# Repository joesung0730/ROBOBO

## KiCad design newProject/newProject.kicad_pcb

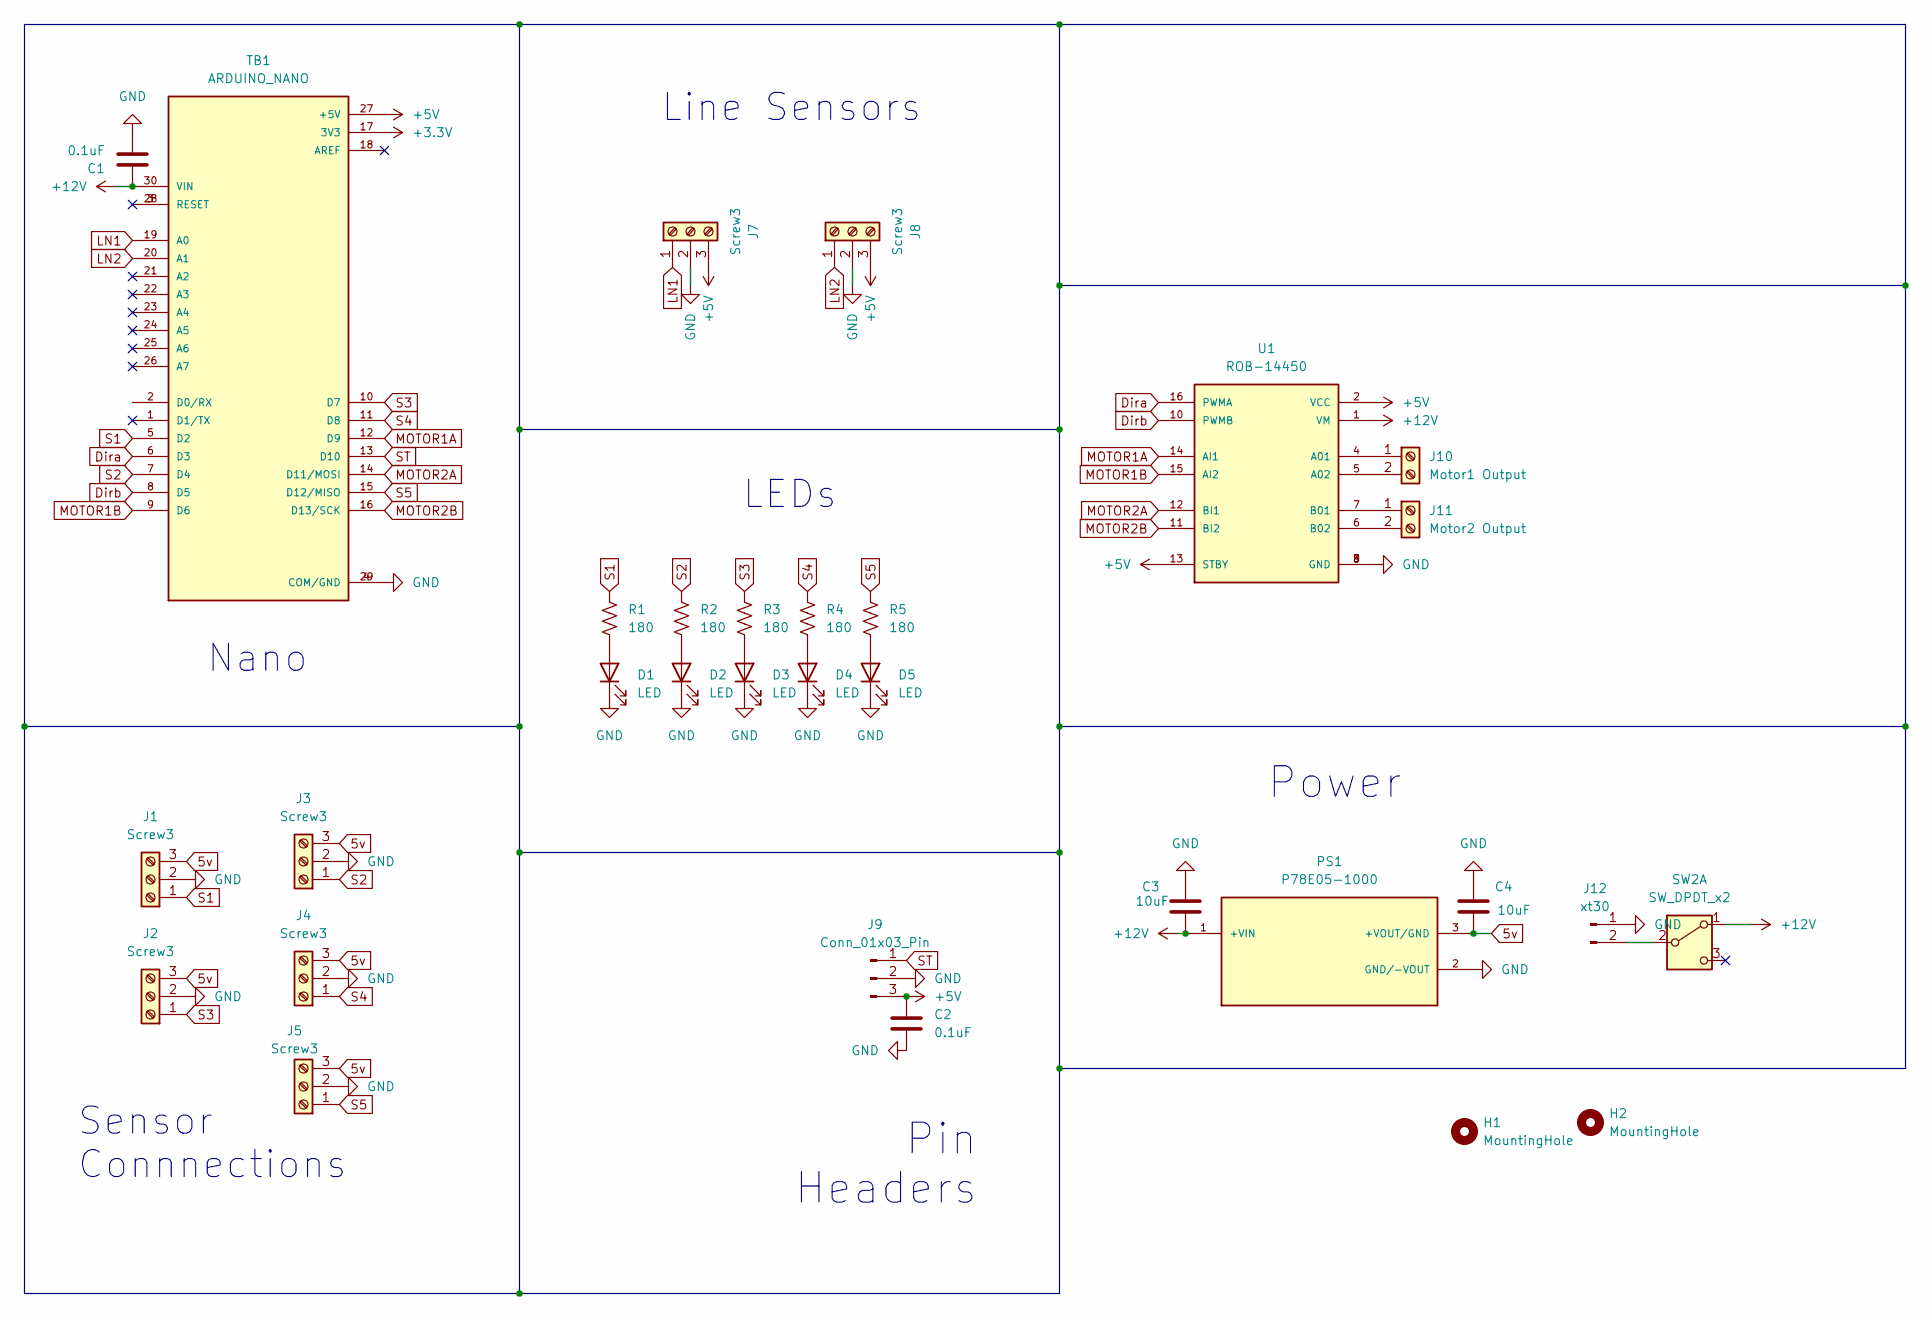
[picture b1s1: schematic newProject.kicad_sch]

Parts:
C1, C2: 0.1uF; C_0805_2012Metric
C3, C4: 10uF; C_0805_2012Metric
D1, D2, D3, D4, D5: LED; LED_1206_3216Metric
H1, H2: MountingHole; MountingHole_2.5mm
J1, J2, J3, J4, J5, J8: Screw3; JST_EH_B3B-EH-A_1x03_P2.50mm_Vertical
J7: Screw3; PinHeader_1x03_P2.54mm_Vertical
J9: Conn_01x03_Pin; PinHeader_1x03_P2.54mm_Vertical
J10: Motor1 Output; PinHeader_1x02_P2.54mm_Vertical
J11: Motor2 Output; PinHeader_1x02_P2.54mm_Vertical
J12: xt30; AMASS_XT30U-F_1x02_P5.0mm_Vertical
PS1: P78E05-1000; CONV_P78E05-1000
R1, R2, R3, R4, R5: 180; R_0805_2012Metric
SW2: SW_DPDT_x2; PinHeader_1x03_P2.54mm_Vertical
TB1: ARDUINO_NANO; Arduino_Nano
U1: ROB-14450; MODULE_ROB-14450; PARTREV 11-13-17

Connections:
5v: C4.1, J1.3, J2.3, J3.3, J4.3, J5.3, PS1.3 (+VOUT/GND)
+3.3V: TB1.17 (3V3)
+5V: C2.1, J7.3, J8.3, J9.3, TB1.27 (+5V), U1.2 (VCC), U1.13 (STBY)
+12V: C1.1, C3.1, PS1.1 (+VIN), SW2.1 (A), TB1.30 (VIN), U1.1 (VM)
Dira: TB1.6 (D3), U1.16 (PWMA)
Dirb: TB1.8 (D5), U1.10 (PWMB)
GND: C1.2, C2.2, C3.2, C4.2, D1.1 (K), D2.1 (K), D3.1 (K), D4.1 (K), D5.1 (K), J1.2, J2.2, J3.2, J4.2, J5.2, J7.2, J8.2, J9.2, J12.1, PS1.2 (GND/-VOUT), TB1.4 (COM/GND), TB1.29 (COM/GND), U1.3 (GND), U1.8 (GND), U1.9 (GND)
LN1: J7.1, TB1.19 (A0)
LN2: J8.1, TB1.20 (A1)
MOTOR1A: TB1.12 (D9), U1.14 (AI1)
MOTOR1B: TB1.9 (D6), U1.15 (AI2)
MOTOR2A: TB1.14 (D11/MOSI), U1.12 (BI1)
MOTOR2B: TB1.16 (D13/SCK), U1.11 (BI2)
unnamed: D1.2 (A), R1.2
unnamed: D2.2 (A), R2.2
unnamed: D3.2 (A), R3.2
unnamed: D4.2 (A), R4.2
unnamed: D5.2 (A), R5.2
unnamed: J10.1, U1.4 (A01)
unnamed: J10.2, U1.5 (A02)
unnamed: J11.1, U1.7 (B01)
unnamed: J11.2, U1.6 (B02)
unnamed: J12.2, SW2.2 (B)
S1: J1.1, R1.1, TB1.5 (D2)
S2: J3.1, R2.1, TB1.7 (D4)
S3: J2.1, R3.1, TB1.10 (D7)
S4: J4.1, R4.1, TB1.11 (D8)
S5: J5.1, R5.1, TB1.15 (D12/MISO)
ST: J9.1, TB1.13 (D10)

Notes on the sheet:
Sensor Connnections
Nano
Power
LEDs
Pin Headers
Line Sensors

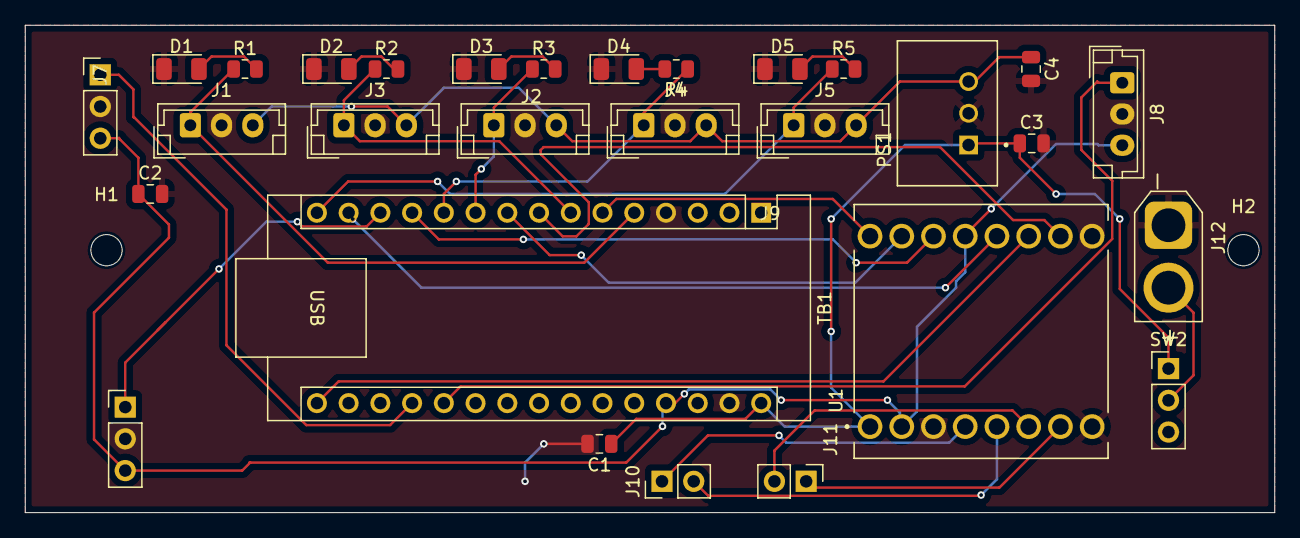
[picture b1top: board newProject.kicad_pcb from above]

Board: 2 copper layers, 100.0 x 39.0 mm, 31 parts (0 on the bottom side), 28 nets.

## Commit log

2025-03-14 new push
2025-03-14 added arduino
2025-03-27 update schematics
2025-03-28 final update
2025-04-07 stuff
